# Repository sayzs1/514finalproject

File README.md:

# 514finalproject
## battery estimate datasheet
display device (https://docs.google.com/spreadsheets/d/1Fs5N1xexbV84x_a7rraujws7_rJ7wwqp-ucotN-aB_U/edit#gid=1736231862)

sensor device (https://docs.google.com/spreadsheets/d/1yTdoJ2G-WuFVsdiDZFG5gB1jXGIMEwbrjy6sTowYsGw/edit#gid=456446529)

## Package presence detect
The project consists of two parts, display device and sense device, which are independently powered by batteries. The purpose of the device is to detect packages at the door and alert people inside to pick them up in time.

## sensor device

## display device

## Communication

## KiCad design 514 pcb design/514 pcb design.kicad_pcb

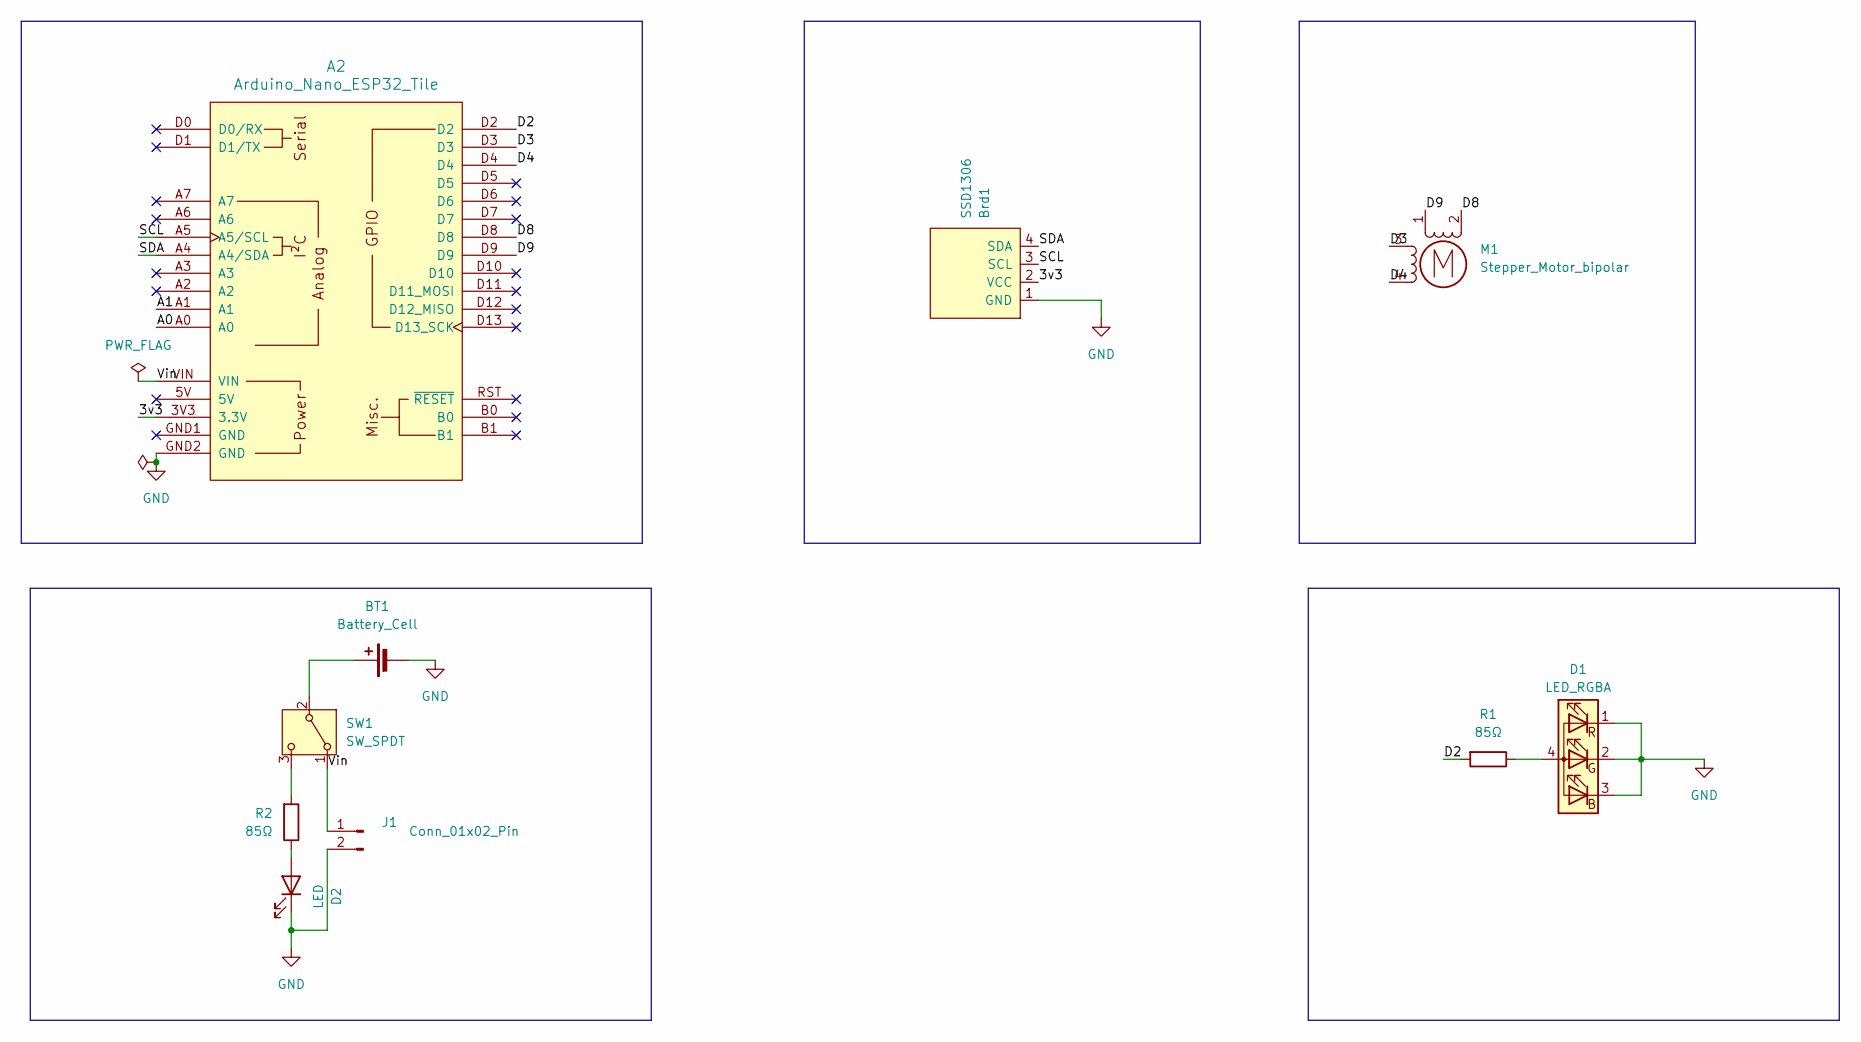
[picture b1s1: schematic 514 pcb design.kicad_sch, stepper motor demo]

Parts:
A2: Arduino_Nano_ESP32_Tile
BT1: Battery_Cell; JST_PHD_B8B-PHDSS_2x04_P2.00mm_Vertical
Brd1: SSD1306; 128x64OLED
D1: LED_RGBA; LED_SK6812_PLCC4_5.0x5.0mm_P3.2mm
D2: LED; LED_0805_2012Metric_Pad1.15x1.40mm_HandSolder
J1: Conn_01x02_Pin; JST_XA_B02B-XASK-1-A_1x02_P2.50mm_Vertical
M1: Stepper_Motor_bipolar; x27_stepper
R1, R2: 85Ω; R_0805_2012Metric_Pad1.20x1.40mm_HandSolder
SW1: SW_SPDT; JST_EH_B3B-EH-A_1x03_P2.50mm_Vertical

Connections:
/3v3: A2.3V3 (3.3V), Brd1.2 (VCC)
/A0: A2.A0
/A1: A2.A1
/D2: A2.D2, R1.2
/D3: A2.D3, M1.3
/D4: A2.D4, M1.4
/D8: A2.D8, M1.2 (-)
/D9: A2.D9, M1.1
/SCL: A2.A5 (A5/SCL), Brd1.3 (SCL)
/SDA: A2.A4 (A4/SDA), Brd1.4 (SDA)
/Vin: A2.VIN, J1.1, SW1.1 (A)
GND: A2.GND2 (GND), BT1.2 (-), Brd1.1 (GND), D1.1 (RK), D1.2 (GK), D1.3 (BK), D2.1 (K), J1.2
unnamed: BT1.1 (+), SW1.2 (B)
unnamed: D1.4 (A), R1.1
unnamed: D2.2 (A), R2.1
unnamed: R2.2, SW1.3 (C)

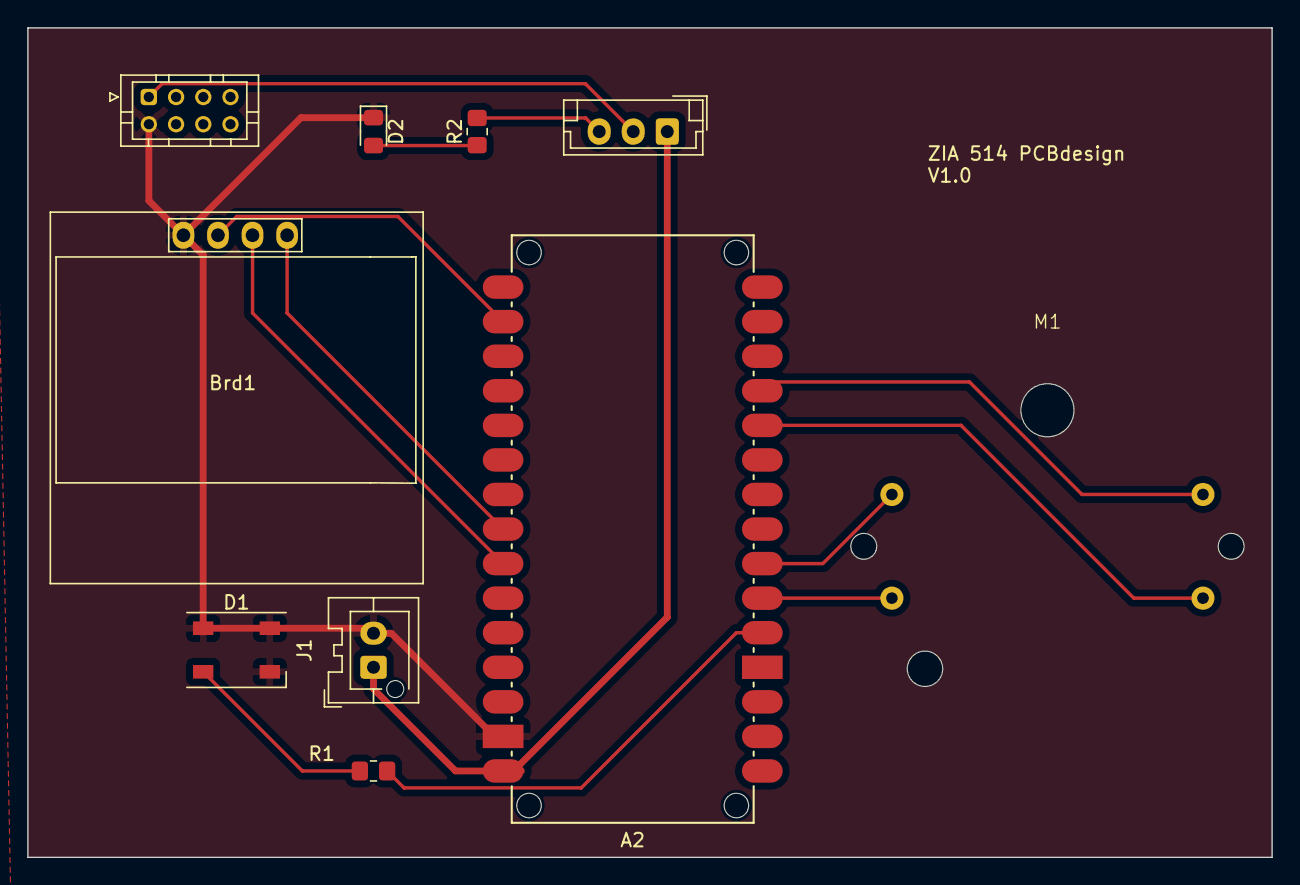
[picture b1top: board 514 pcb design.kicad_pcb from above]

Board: 2 copper layers, 91.4 x 61.0 mm, 10 parts (0 on the bottom side), 14 nets.

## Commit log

2024-01-15 upload datasheet
2024-01-15 create media
2024-01-15 update files
2024-01-16 update sketch
2024-01-17 update sketch and diagram
2024-01-17 correct the pic url
2024-01-17 create kicad folder
2024-02-07 new datasheet
